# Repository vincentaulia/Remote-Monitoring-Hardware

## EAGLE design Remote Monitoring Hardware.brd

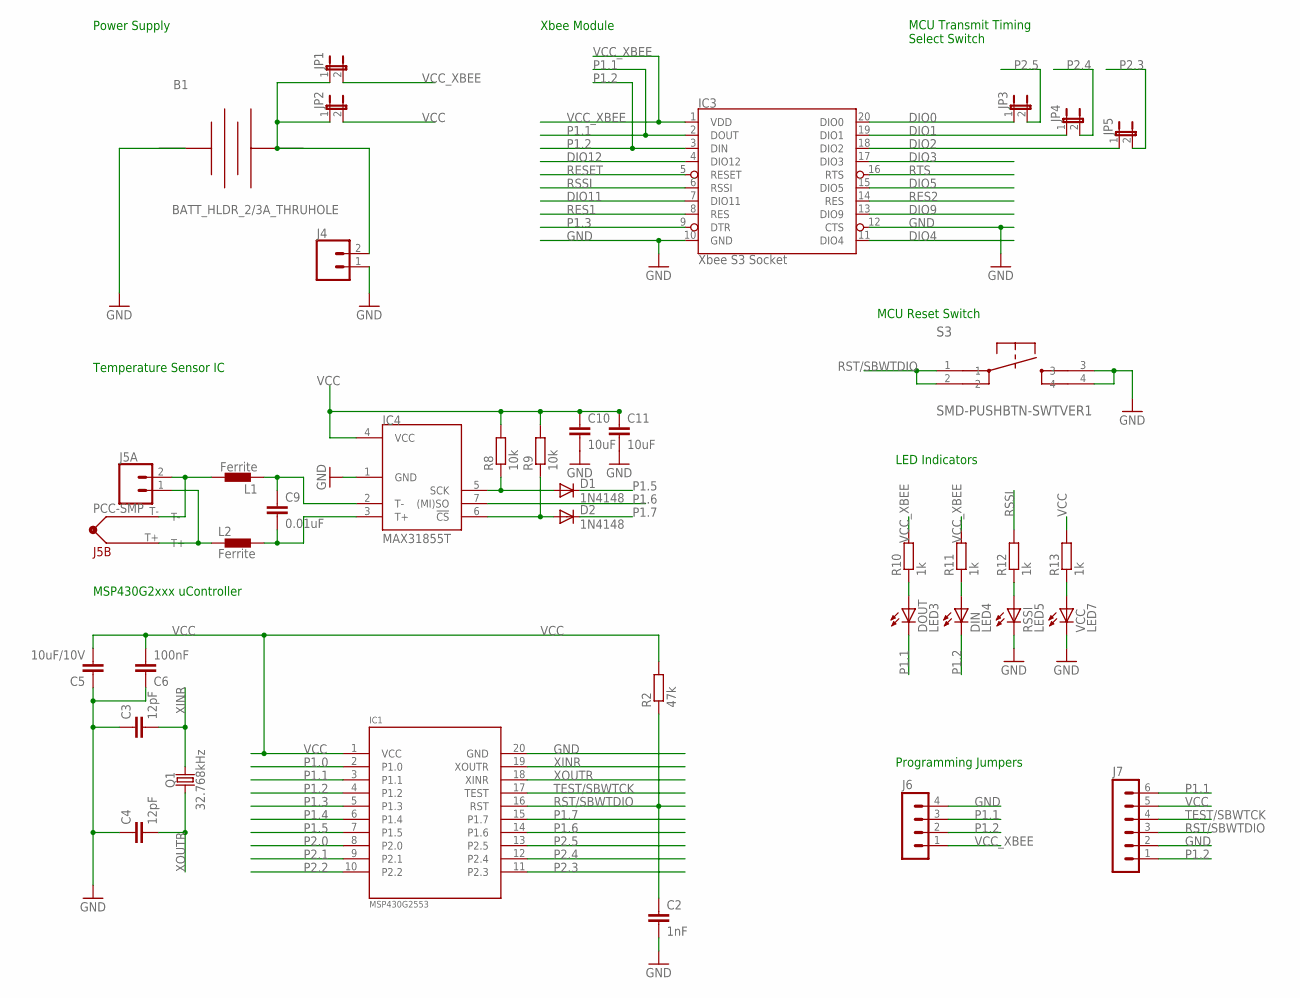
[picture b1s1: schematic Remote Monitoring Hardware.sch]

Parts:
B1: BATT_HLDR_2/3A_THRUHOLE
C2: 1nF; C0805
C3, C4: 12pF; C0805
C5: 10uF/10V; C0805
C6: 100nF; C0805
C9: 0.01uF; C0805
C10, C11: 10uF; C0805
D1, D2: 1N4148; SOD323-R
DIN: LED4; SML0805
DOUT: LED3; SML0805
IC1: MSP430G2553; MSP430G2553IPW20
IC3: Xbee S3 Socket; XBEE-LONGPAD
IC4: MAX31855T; SOIC8
J4, J5A: CONN_023.5MM; SCREWTERMINAL-3.5MM-2
J5B: PCC-SMP
J6: MA04-1
J7: MA06-1
JP1, JP2, JP3, JP4, JP5: JUMPER-2PTH; 1X02
L1, L2: Ferrite; 0402
Q1: 32.768kHz; CRYSTAL-SMD-2X6-CYL
R2: 47k; R0805
R8, R9: 10k; R0805
R10, R11, R12, R13: 1k; R0805
RSSI: LED5; SML0805
S3: SMD-PUSHBTN-SWTVER1; KPT-1187B
VCC: LED7; SML0805

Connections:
1: D1.A, IC4.5 (SCK), R8.1
2: D2.A, IC4.6 (!CS), R9.1
DIO0: IC3.20 (DIO0), JP3.1
DIO1: IC3.19 (DIO1), JP4.1
DIO2: IC3.18 (DIO2), JP5.1
DIO3: IC3.17 (DIO3)
DIO4: IC3.11 (DIO4)
DIO5: IC3.15 (DIO5)
DIO9: IC3.13 (DIO9)
DIO11: IC3.7 (DIO11)
DIO12: IC3.4 (DIO12)
GND: B1.NEG, C2.2, C3.1, C4.1, C5.1, C6.1, C10.2, C11.2, IC1.20 (GND), IC3.10 (GND), IC3.12 (CTS), IC4.1 (GND), J4.1, J6.4, J7.2, RSSI.C, S3.3, S3.4, VCC.C
unnamed: B1.POS, J4.2, JP1.1, JP2.1
unnamed: DOUT.A, R10.1
unnamed: DIN.A, R11.1
unnamed: R12.1, RSSI.A
unnamed: C9.1, IC4.2 (T-), L1.1
unnamed: C9.2, IC4.3 (T+), L2.2
unnamed: J5A.2, J5B.T-, L1.2
unnamed: J5A.1, J5B.T+, L2.1
unnamed: R13.1, VCC.A
P1.0: IC1.2 (P1.0)
P1.1: DOUT.C, IC1.3 (P1.1), IC3.2 (DOUT), J6.3, J7.6
P1.2: DIN.C, IC1.4 (P1.2), IC3.3 (DIN), J6.2, J7.1
P1.3: IC1.5 (P1.3), IC3.9 (DTR)
P1.4: IC1.6 (P1.4)
P1.5: D1.C, IC1.7 (P1.5)
P1.6: IC1.14 (P1.6), IC4.7 ((MI)SO)
P1.7: D2.C, IC1.15 (P1.7)
P2.0: IC1.8 (P2.0)
P2.1: IC1.9 (P2.1)
P2.2: IC1.10 (P2.2)
P2.3: IC1.11 (P2.3), JP5.2
P2.4: IC1.12 (P2.4), JP4.2
P2.5: IC1.13 (P2.5), JP3.2
RES1: IC3.8 (RES)
RES2: IC3.14 (RES)
RESET: IC3.5 (RESET)
RSSI: IC3.6 (RSSI), R12.2
RST/SBWTDIO: C2.1, IC1.16 (RST), J7.3, R2.1, S3.1, S3.2
RTS: IC3.16 (RTS)
TEST/SBWTCK: IC1.17 (TEST), J7.4
VCC: C5.2, C6.2, C10.1, C11.1, IC1.1 (VCC), IC4.4 (VCC), J7.5, JP2.2, R2.2, R8.2, R9.2, R13.2
VCC_XBEE: IC3.1 (VDD), J6.1, JP1.2, R10.2, R11.2
XINR: C3.2, IC1.19 (XOUTR), Q1.X2 (2)
XOUTR: C4.2, IC1.18 (XINR), Q1.X1 (1)

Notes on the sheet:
Power Supply
Xbee Module
LED Indicators
Temperature Sensor IC
MSP430G2xxx uController
MCU Reset Switch
Programming Jumpers
MCU Transmit Timing Select Switch

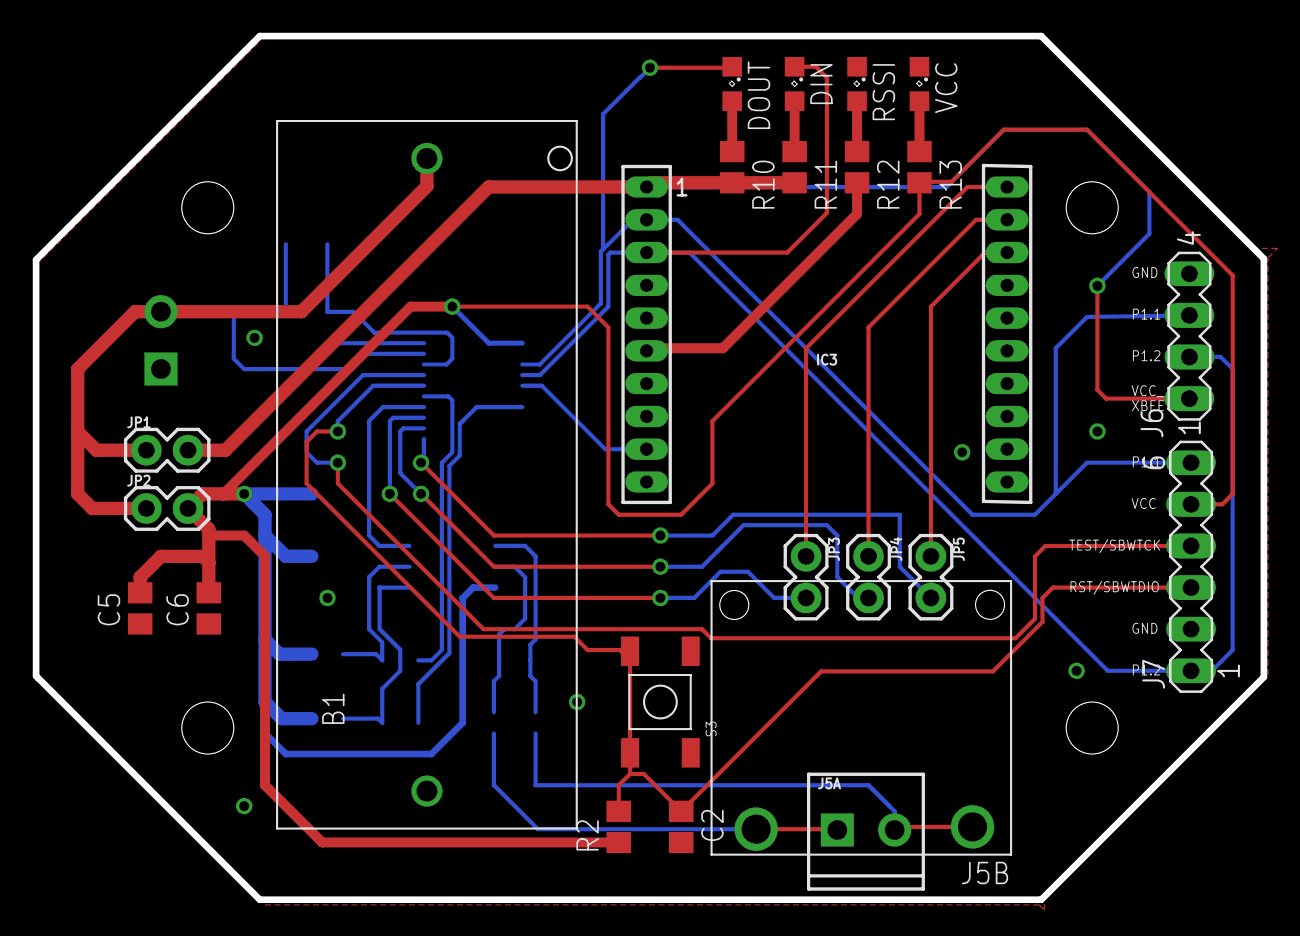
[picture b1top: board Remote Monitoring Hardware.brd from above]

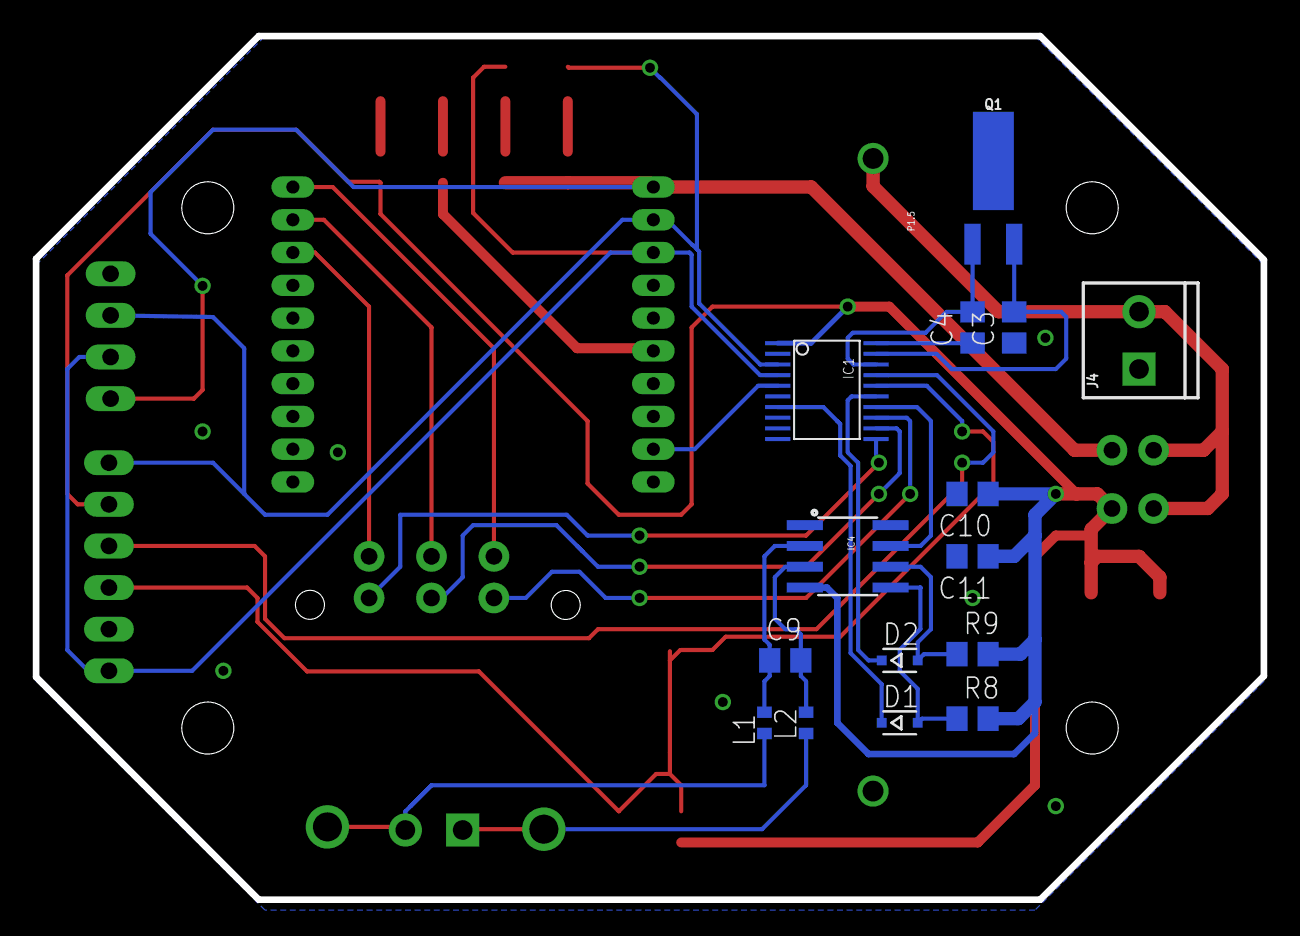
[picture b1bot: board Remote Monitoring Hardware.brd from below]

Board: 2 copper layers, 74.9 x 52.7 mm, 39 parts (15 on the bottom side), 31 nets.

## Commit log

2017-09-20 initial project version
2017-09-20 board and schematics update May 25 2017
2017-09-20 Added BOM + brd & sch changes Aug 28 2017
2017-09-20 brd & sch changes Sept 12 2017
2017-09-20 brd sch BOM changes Sept 20 2017
2017-09-20 larger msp430 programmer pins , new eagle project setup
2017-09-20 revised bom for larger programming pin

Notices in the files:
parts and their libraries:
SparkFun-RF: Licensing: Creative Commons ShareAlike 4.0 International - https://creativecommons.org/licenses/by-sa/4.0
